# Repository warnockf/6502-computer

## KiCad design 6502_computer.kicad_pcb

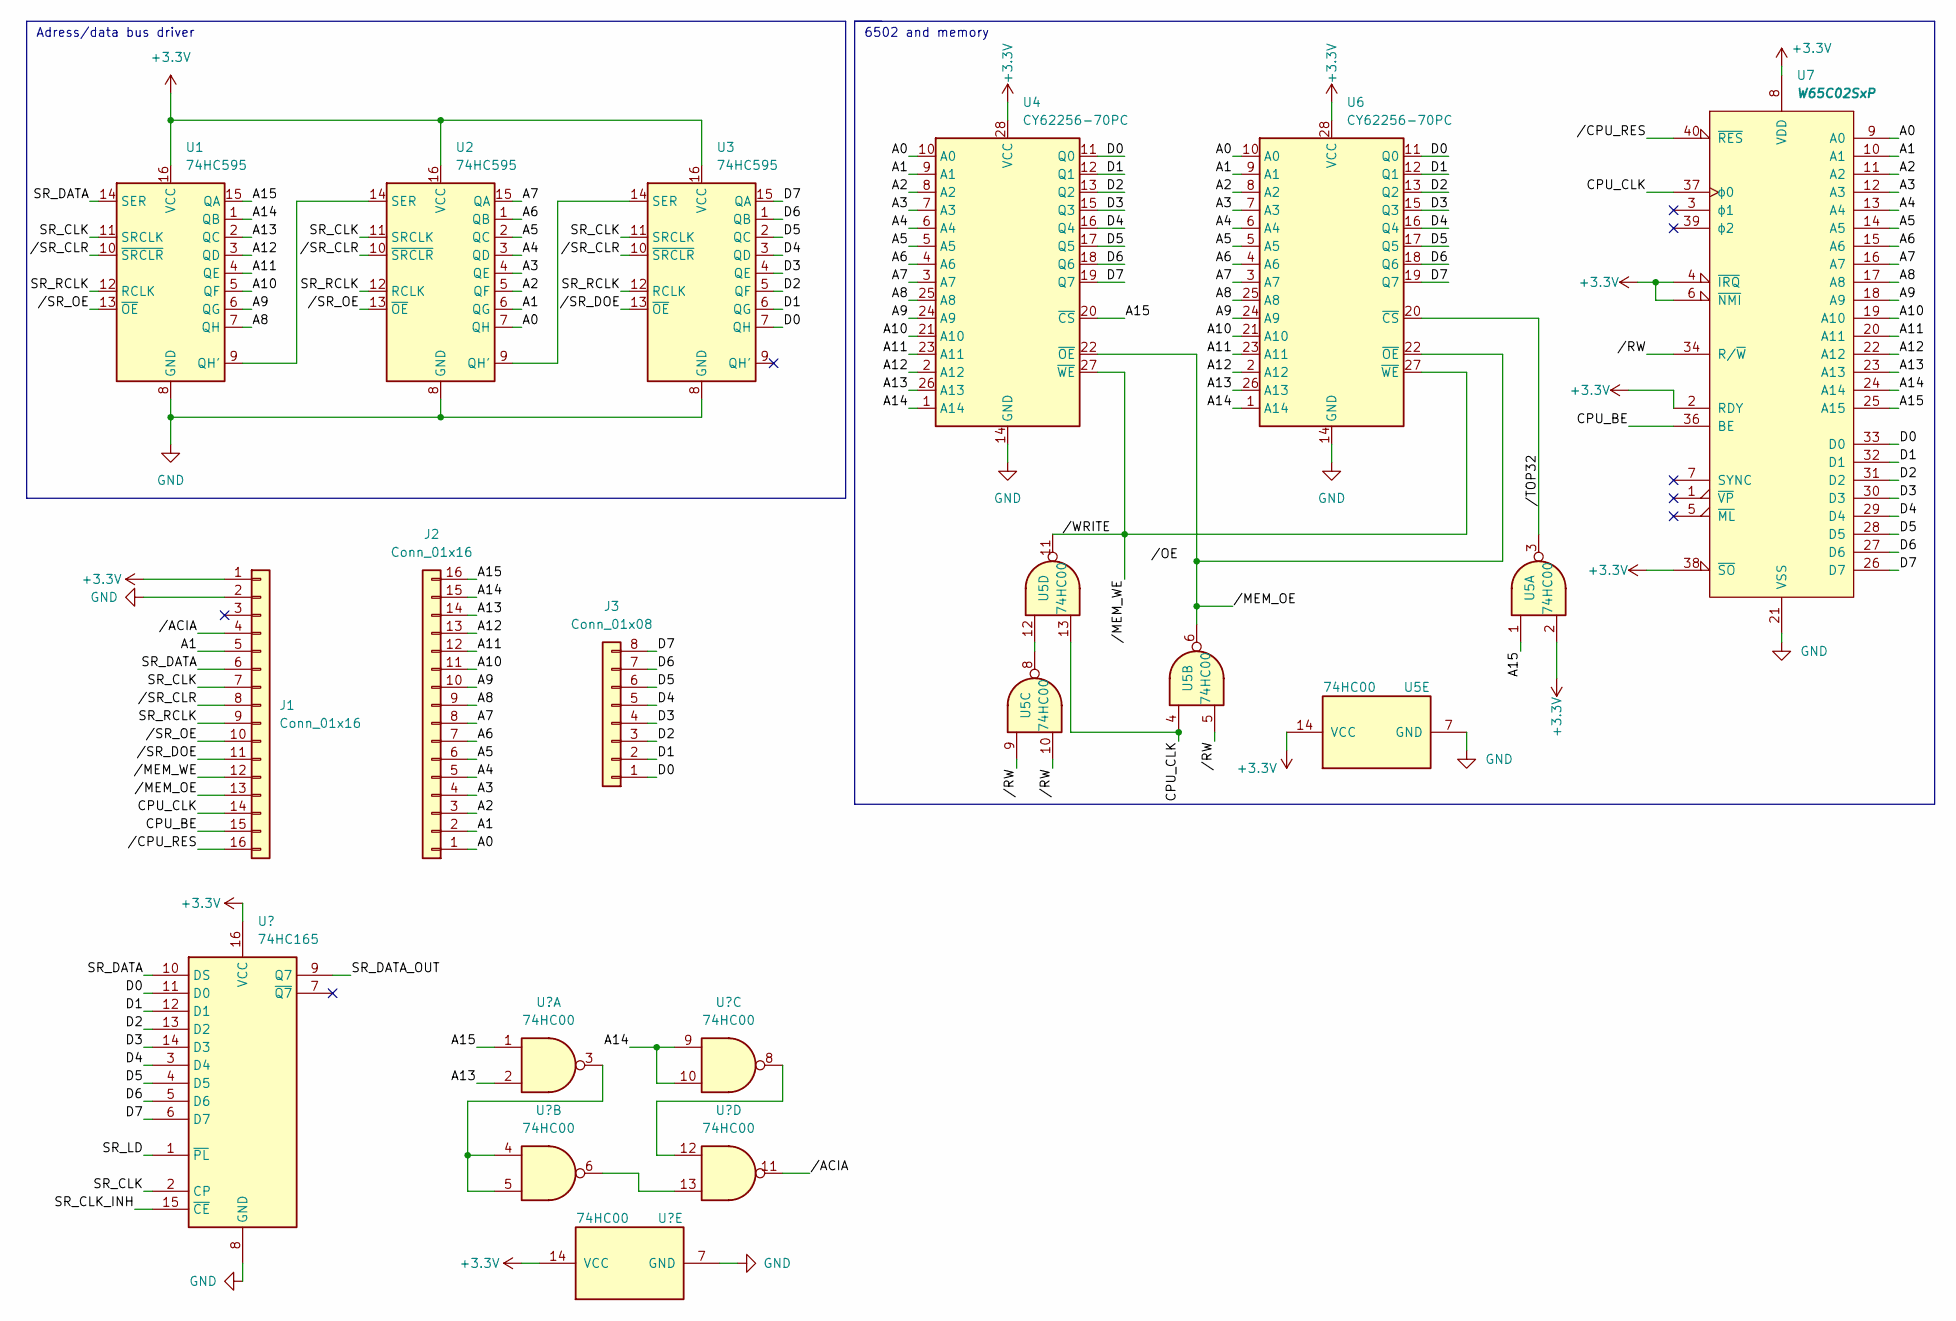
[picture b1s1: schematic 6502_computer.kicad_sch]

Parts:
J1, J2: Conn_01x16; PinSocket_1x16_P2.54mm_Vertical
J3: Conn_01x08; PinHeader_1x08_P2.54mm_Vertical
U1, U2, U3: 74HC595; DIP-16_W7.62mm
U4, U6: CY62256-70PC; DIP-28_W15.24mm_Socket
U5: 74HC00; DIP-14_W7.62mm
U7: W65C02SxP; DIP-40_W15.24mm_Socket

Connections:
+3.3V: J1.1, U1.16 (VCC), U2.16 (VCC), U3.16 (VCC), U4.28 (VCC), U5.2, U5.14 (VCC), U6.28 (VCC), U7.2 (RDY), U7.4 (~IRQ), U7.6 (~NMI), U7.8 (VDD), U7.38 (~SO)
/A0: J2.1, U2.7 (QH), U4.10 (A0), U6.10 (A0), U7.9 (A0)
/A1: J1.5, J2.2, U2.6 (QG), U4.9 (A1), U6.9 (A1), U7.10 (A1)
/A2: J2.3, U2.5 (QF), U4.8 (A2), U6.8 (A2), U7.11 (A2)
/A3: J2.4, U2.4 (QE), U4.7 (A3), U6.7 (A3), U7.12 (A3)
/A4: J2.5, U2.3 (QD), U4.6 (A4), U6.6 (A4), U7.13 (A4)
/A5: J2.6, U2.2 (QC), U4.5 (A5), U6.5 (A5), U7.14 (A5)
/A6: J2.7, U2.1 (QB), U4.4 (A6), U6.4 (A6), U7.15 (A6)
/A7: J2.8, U2.15 (QA), U4.3 (A7), U6.3 (A7), U7.16 (A7)
/A8: J2.9, U1.7 (QH), U4.25 (A8), U6.25 (A8), U7.17 (A8)
/A9: J2.10, U1.6 (QG), U4.24 (A9), U6.24 (A9), U7.18 (A9)
/A10: J2.11, U1.5 (QF), U4.21 (A10), U6.21 (A10), U7.19 (A10)
/A11: J2.12, U1.4 (QE), U4.23 (A11), U6.23 (A11), U7.20 (A11)
/A12: J2.13, U1.3 (QD), U4.2 (A12), U6.2 (A12), U7.22 (A12)
/A13: J2.14, U1.2 (QC), U4.26 (A13), U6.26 (A13), U7.23 (A13)
/A14: J2.15, U1.1 (QB), U4.1 (A14), U6.1 (A14), U7.24 (A14)
/A15: J2.16, U1.15 (QA), U4.20 (~CS), U5.1, U7.25 (A15)
/CPU_BE: J1.15, U7.36 (BE)
/CPU_CLK: J1.14, U5.4, U5.13, U7.37 (ϕ0)
/D0: J3.1, U3.7 (QH), U4.11 (Q0), U6.11 (Q0), U7.33 (D0)
/D1: J3.2, U3.6 (QG), U4.12 (Q1), U6.12 (Q1), U7.32 (D1)
/D2: J3.3, U3.5 (QF), U4.13 (Q2), U6.13 (Q2), U7.31 (D2)
/D3: J3.4, U3.4 (QE), U4.15 (Q3), U6.15 (Q3), U7.30 (D3)
/D4: J3.5, U3.3 (QD), U4.16 (Q4), U6.16 (Q4), U7.29 (D4)
/D5: J3.6, U3.2 (QC), U4.17 (Q5), U6.17 (Q5), U7.28 (D5)
/D6: J3.7, U3.1 (QB), U4.18 (Q6), U6.18 (Q6), U7.27 (D6)
/D7: J3.8, U3.15 (QA), U4.19 (Q7), U6.19 (Q7), U7.26 (D7)
/SR_CLK: J1.7, U1.11 (SRCLK), U2.11 (SRCLK), U3.11 (SRCLK)
/SR_DATA: J1.6, U1.14 (SER)
/SR_RCLK: J1.9, U1.12 (RCLK), U2.12 (RCLK), U3.12 (RCLK)
//CPU_RES: J1.16, U7.40 (~RES)
//MEM_OE: J1.13, U4.22 (~OE), U5.6, U6.22 (~OE)
//MEM_WE: J1.12, U4.27 (~WE), U5.11, U6.27 (~WE)
//RW: U5.5, U5.9, U5.10, U7.34 (R/~W)
//SR_CLR: J1.8, U1.10 (~SRCLR), U2.10 (~SRCLR), U3.10 (~SRCLR)
//SR_DOE: J1.11, U3.13 (~OE)
//SR_OE: J1.10, U1.13 (~OE), U2.13 (~OE)
//TOP32: U5.3, U6.20 (~CS)
GND: J1.2, U1.8 (GND), U2.8 (GND), U3.8 (GND), U4.14 (GND), U5.7 (GND), U6.14 (GND), U7.21 (VSS)
unnamed: U1.9 (QH'), U2.14 (SER)
unnamed: U2.9 (QH'), U3.14 (SER)
unnamed: U5.8, U5.12

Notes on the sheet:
Adress/data bus driver
6502 and memory

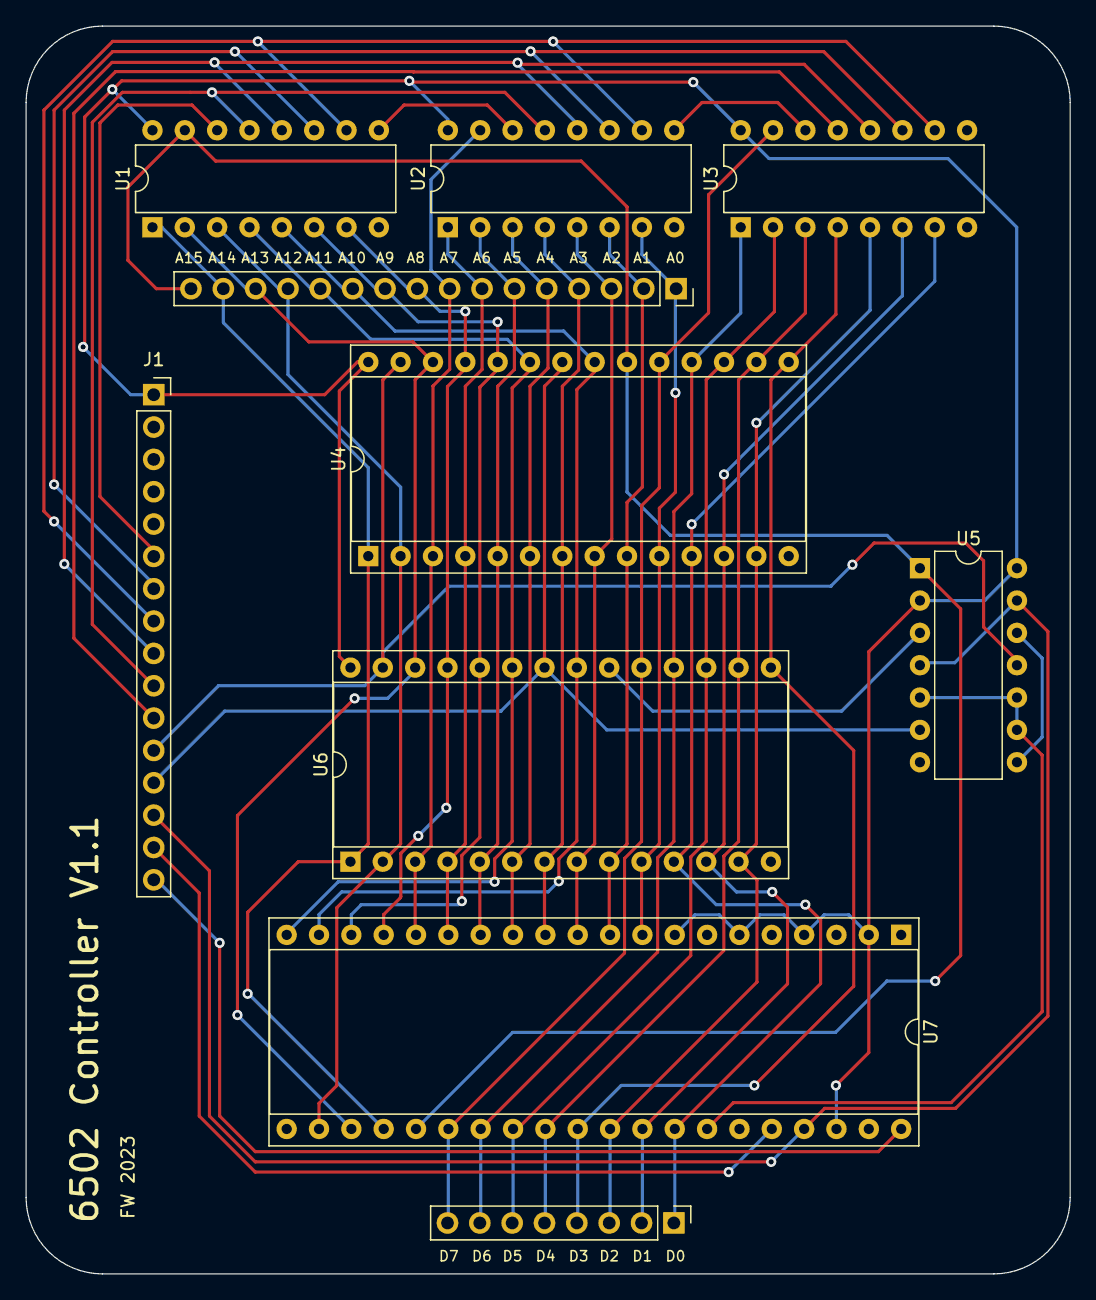
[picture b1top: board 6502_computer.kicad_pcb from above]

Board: 2 copper layers, 82.0 x 98.0 mm, 10 parts (0 on the bottom side), 42 nets.
